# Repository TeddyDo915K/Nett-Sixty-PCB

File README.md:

# Nett Sixty PCB (An Inett Square X Replacement PCB)
This is a work in progress to create a replacement PCB for one of my favorite keyboards that I own.

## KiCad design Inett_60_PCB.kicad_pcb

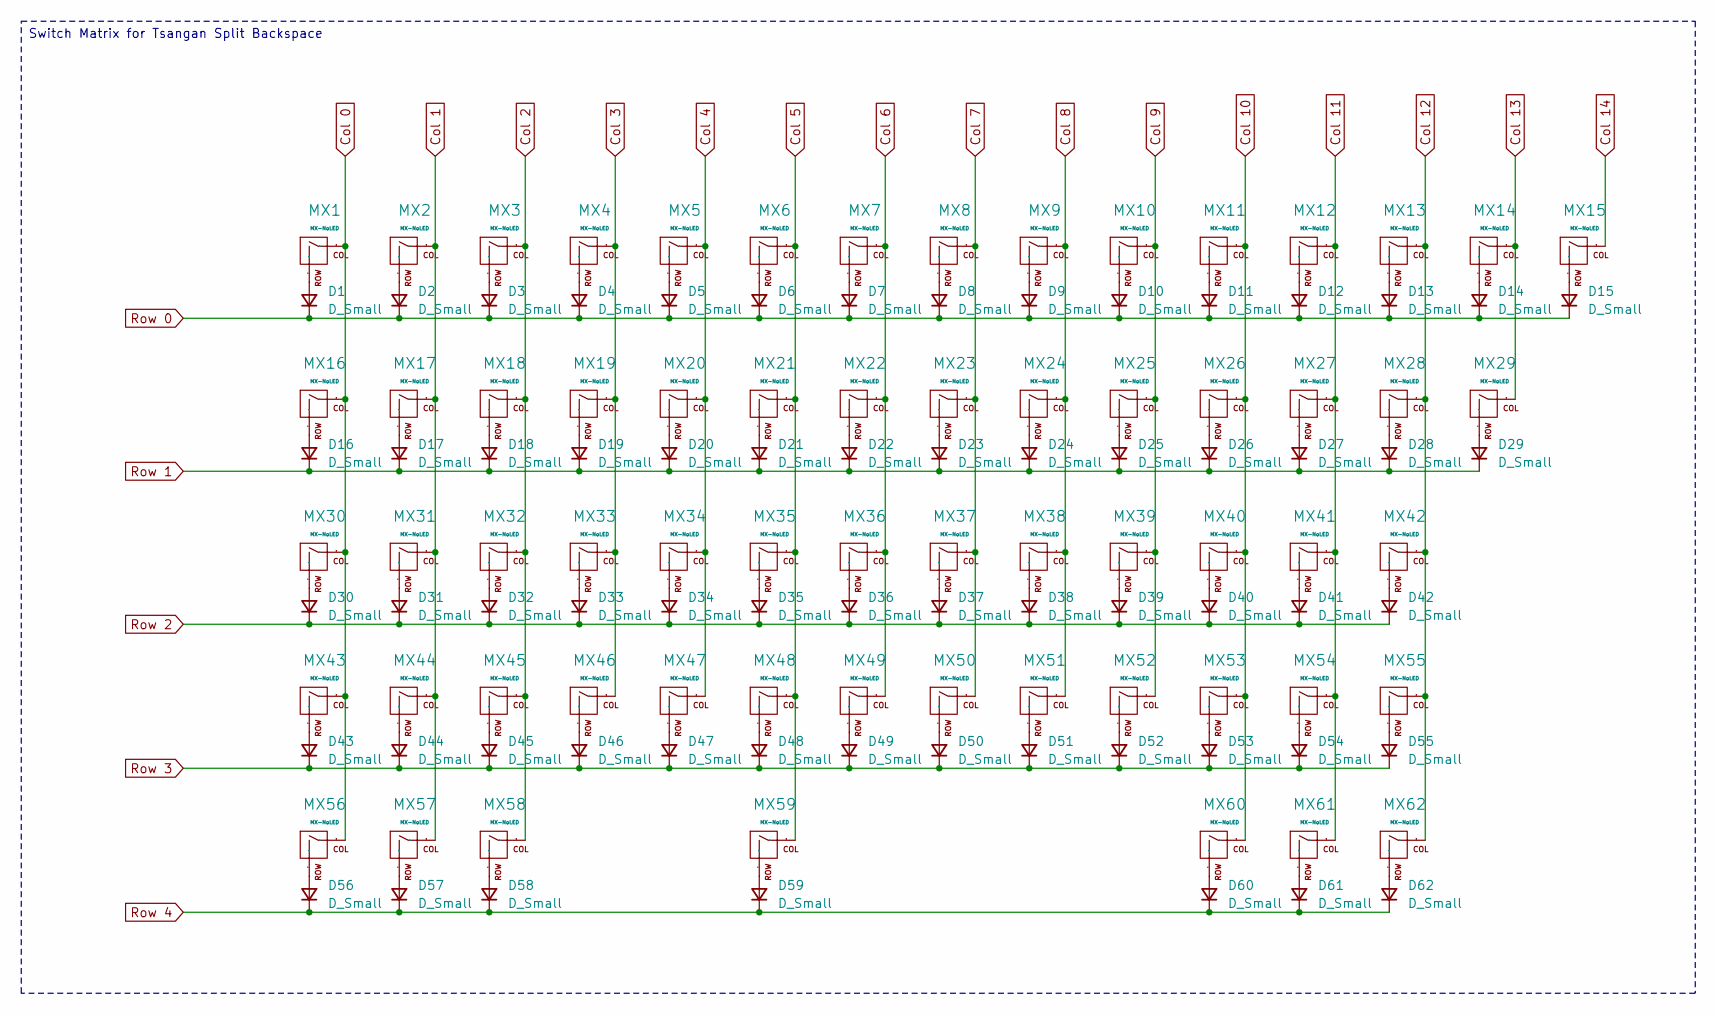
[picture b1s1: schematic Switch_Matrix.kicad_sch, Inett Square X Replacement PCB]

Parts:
D1, D2, D3, D4, D5, D6, D7, D8, D9, D10, D11, D12, D13, D14, D15, D16, D17, D18, D19, D20, D21, D22, D23, D24, D25, D26, D27, D28, D29, D30, D31, D32, D33, D34, D35, D36, D37, D38, D39, D40, D41, D42, D43, D44, D45, D46, D47, D48, D49, D50, D51, D52, D53, D54, D55, D56, D57, D58, D59, D60, D61, D62: D_Small; D_SOD-123
MX1, MX2, MX3, MX4, MX5, MX6, MX7, MX8, MX9, MX10, MX11, MX12, MX13, MX14, MX15, MX17, MX18, MX19, MX20, MX21, MX22, MX23, MX24, MX25, MX26, MX27, MX28, MX31, MX32, MX33, MX34, MX35, MX36, MX37, MX38, MX39, MX40, MX41, MX44, MX45, MX46, MX47, MX48, MX49, MX50, MX51, MX52, MX53, MX55, MX57, MX61: MX-NoLED; MXOnly-1U-Hotswap
MX16, MX29, MX56, MX58, MX60, MX62: MX-NoLED; MXOnly-1.5U-Hotswap
MX30, MX54: MX-NoLED; MXOnly-1.75U-Hotswap
MX42, MX43: MX-NoLED; MXOnly-2.25U-Hotswap
MX59: MX-NoLED; MXOnly-7U-Hotswap-ReversedStabilizers

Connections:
Col 0: MX1.1 (COL), MX16.1 (COL), MX30.1 (COL), MX43.1 (COL), MX56.1 (COL); also elsewhere on the board
Col 1: MX2.1 (COL), MX17.1 (COL), MX31.1 (COL), MX44.1 (COL), MX57.1 (COL); also elsewhere on the board
Col 2: MX3.1 (COL), MX18.1 (COL), MX32.1 (COL), MX45.1 (COL), MX58.1 (COL); also elsewhere on the board
Col 3: MX4.1 (COL), MX19.1 (COL), MX33.1 (COL), MX46.1 (COL); also elsewhere on the board
Col 4: MX5.1 (COL), MX20.1 (COL), MX34.1 (COL), MX47.1 (COL); also elsewhere on the board
Col 5: MX6.1 (COL), MX21.1 (COL), MX35.1 (COL), MX48.1 (COL), MX59.1 (COL); also elsewhere on the board
Col 6: MX7.1 (COL), MX22.1 (COL), MX36.1 (COL), MX49.1 (COL); also elsewhere on the board
Col 7: MX8.1 (COL), MX23.1 (COL), MX37.1 (COL), MX50.1 (COL); also elsewhere on the board
Col 8: MX9.1 (COL), MX24.1 (COL), MX38.1 (COL), MX51.1 (COL); also elsewhere on the board
Col 9: MX10.1 (COL), MX25.1 (COL), MX39.1 (COL), MX52.1 (COL); also elsewhere on the board
Col 10: MX11.1 (COL), MX26.1 (COL), MX40.1 (COL), MX53.1 (COL), MX60.1 (COL); also elsewhere on the board
Col 11: MX12.1 (COL), MX27.1 (COL), MX41.1 (COL), MX54.1 (COL), MX61.1 (COL); also elsewhere on the board
Col 12: MX13.1 (COL), MX28.1 (COL), MX42.1 (COL), MX55.1 (COL), MX62.1 (COL); also elsewhere on the board
Col 13: MX14.1 (COL), MX29.1 (COL); also elsewhere on the board
Col 14: MX15.1 (COL); also elsewhere on the board
unnamed: D1.2 (A), MX1.2 (ROW)
unnamed: D2.2 (A), MX2.2 (ROW)
unnamed: D3.2 (A), MX3.2 (ROW)
unnamed: D4.2 (A), MX4.2 (ROW)
unnamed: D5.2 (A), MX5.2 (ROW)
unnamed: D6.2 (A), MX6.2 (ROW)
unnamed: D7.2 (A), MX7.2 (ROW)
unnamed: D8.2 (A), MX8.2 (ROW)
unnamed: D9.2 (A), MX9.2 (ROW)
unnamed: D10.2 (A), MX10.2 (ROW)
unnamed: D11.2 (A), MX11.2 (ROW)
unnamed: D12.2 (A), MX12.2 (ROW)
unnamed: D13.2 (A), MX13.2 (ROW)
unnamed: D14.2 (A), MX14.2 (ROW)
unnamed: D15.2 (A), MX15.2 (ROW)
unnamed: D16.2 (A), MX16.2 (ROW)
unnamed: D17.2 (A), MX17.2 (ROW)
unnamed: D18.2 (A), MX18.2 (ROW)
unnamed: D19.2 (A), MX19.2 (ROW)
unnamed: D20.2 (A), MX20.2 (ROW)
unnamed: D21.2 (A), MX21.2 (ROW)
unnamed: D22.2 (A), MX22.2 (ROW)
unnamed: D23.2 (A), MX23.2 (ROW)
unnamed: D24.2 (A), MX24.2 (ROW)
unnamed: D25.2 (A), MX25.2 (ROW)
unnamed: D26.2 (A), MX26.2 (ROW)
unnamed: D27.2 (A), MX27.2 (ROW)
unnamed: D28.2 (A), MX28.2 (ROW)
unnamed: D29.2 (A), MX29.2 (ROW)
unnamed: D30.2 (A), MX30.2 (ROW)
unnamed: D31.2 (A), MX31.2 (ROW)
unnamed: D32.2 (A), MX32.2 (ROW)
unnamed: D33.2 (A), MX33.2 (ROW)
unnamed: D34.2 (A), MX34.2 (ROW)
unnamed: D35.2 (A), MX35.2 (ROW)
unnamed: D36.2 (A), MX36.2 (ROW)
unnamed: D37.2 (A), MX37.2 (ROW)
unnamed: D38.2 (A), MX38.2 (ROW)
unnamed: D39.2 (A), MX39.2 (ROW)
unnamed: D40.2 (A), MX40.2 (ROW)
unnamed: D41.2 (A), MX41.2 (ROW)
unnamed: D42.2 (A), MX42.2 (ROW)
unnamed: D43.2 (A), MX43.2 (ROW)
unnamed: D44.2 (A), MX44.2 (ROW)
unnamed: D45.2 (A), MX45.2 (ROW)
unnamed: D46.2 (A), MX46.2 (ROW)
unnamed: D47.2 (A), MX47.2 (ROW)
unnamed: D48.2 (A), MX48.2 (ROW)
unnamed: D49.2 (A), MX49.2 (ROW)
unnamed: D50.2 (A), MX50.2 (ROW)
unnamed: D51.2 (A), MX51.2 (ROW)
unnamed: D52.2 (A), MX52.2 (ROW)
unnamed: D53.2 (A), MX53.2 (ROW)
unnamed: D54.2 (A), MX54.2 (ROW)
unnamed: D55.2 (A), MX55.2 (ROW)
unnamed: D56.2 (A), MX56.2 (ROW)
unnamed: D57.2 (A), MX57.2 (ROW)
unnamed: D58.2 (A), MX58.2 (ROW)
unnamed: D59.2 (A), MX59.2 (ROW)
unnamed: D60.2 (A), MX60.2 (ROW)
unnamed: D61.2 (A), MX61.2 (ROW)
unnamed: D62.2 (A), MX62.2 (ROW)
Row 0: D1.1 (K), D2.1 (K), D3.1 (K), D4.1 (K), D5.1 (K), D6.1 (K), D7.1 (K), D8.1 (K), D9.1 (K), D10.1 (K), D11.1 (K), D12.1 (K), D13.1 (K), D14.1 (K), D15.1 (K); also elsewhere on the board
Row 1: D16.1 (K), D17.1 (K), D18.1 (K), D19.1 (K), D20.1 (K), D21.1 (K), D22.1 (K), D23.1 (K), D24.1 (K), D25.1 (K), D26.1 (K), D27.1 (K), D28.1 (K), D29.1 (K); also elsewhere on the board
Row 2: D30.1 (K), D31.1 (K), D32.1 (K), D33.1 (K), D34.1 (K), D35.1 (K), D36.1 (K), D37.1 (K), D38.1 (K), D39.1 (K), D40.1 (K), D41.1 (K), D42.1 (K); also elsewhere on the board
Row 3: D43.1 (K), D44.1 (K), D45.1 (K), D46.1 (K), D47.1 (K), D48.1 (K), D49.1 (K), D50.1 (K), D51.1 (K), D52.1 (K), D53.1 (K), D54.1 (K), D55.1 (K); also elsewhere on the board
Row 4: D56.1 (K), D57.1 (K), D58.1 (K), D59.1 (K), D60.1 (K), D61.1 (K), D62.1 (K); also elsewhere on the board

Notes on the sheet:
Switch Matrix for Tsangan Split Backspace

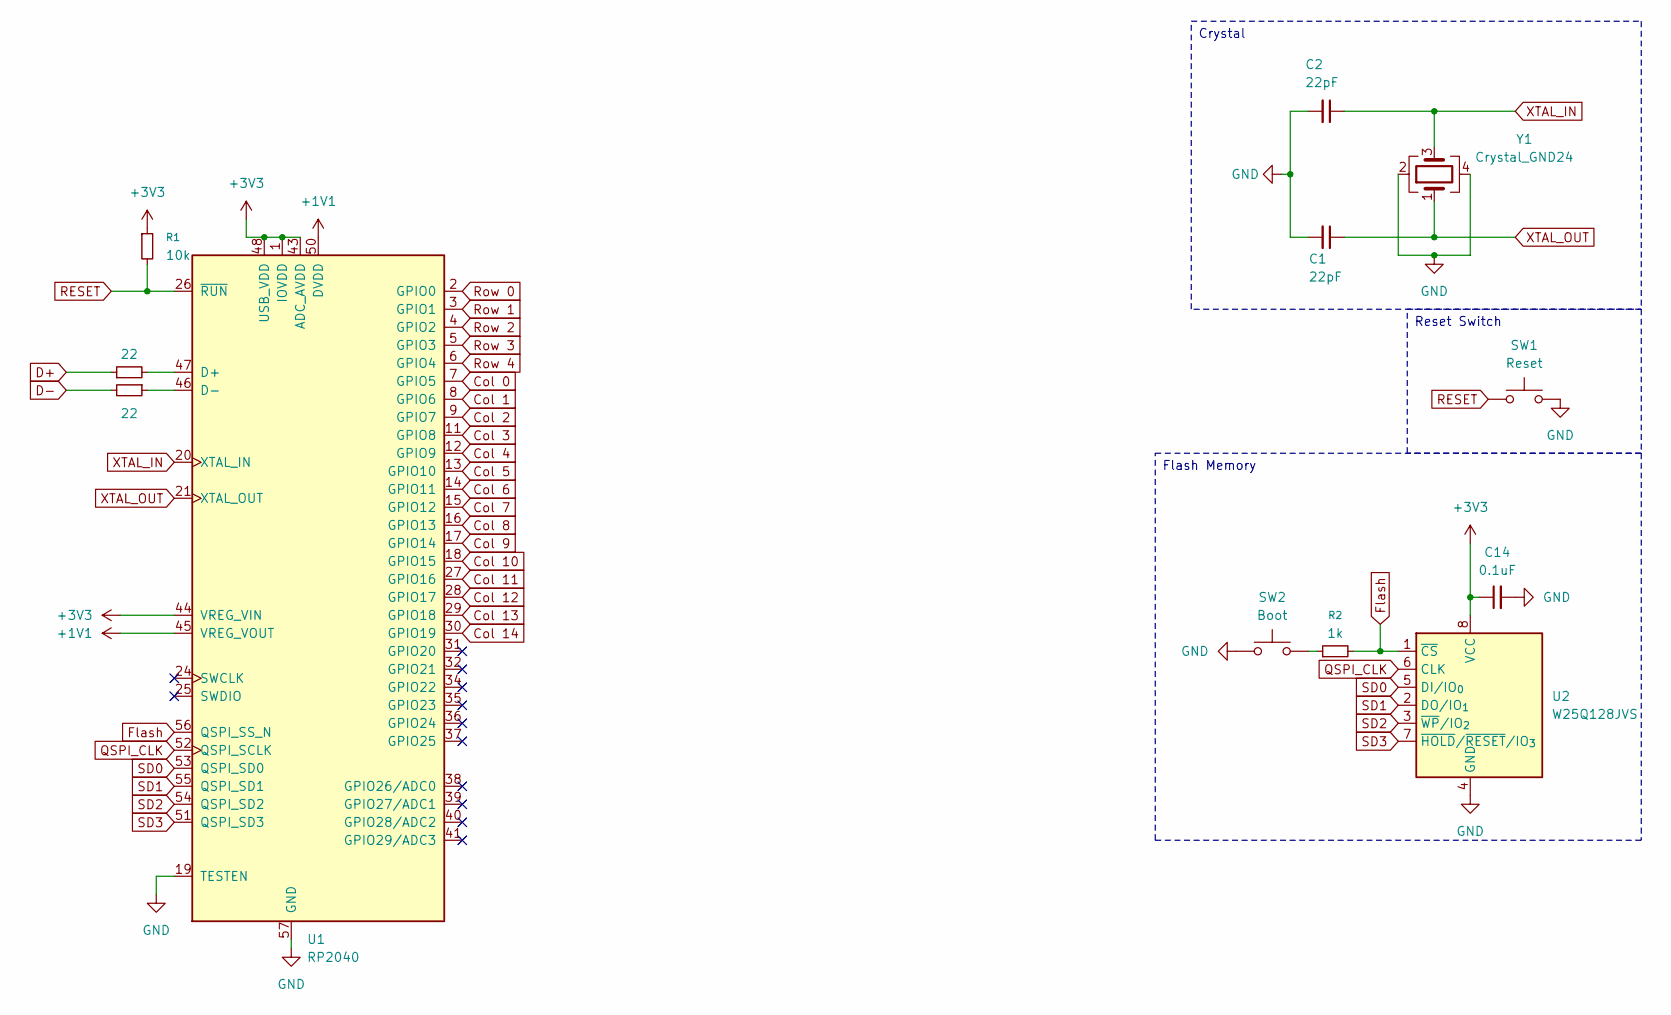
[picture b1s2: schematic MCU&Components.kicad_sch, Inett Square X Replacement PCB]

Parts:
C1, C2: 22pF; C_0402_1005Metric
C14: 0.1uF; C_0402
R1: 10k; R_0805_2012Metric_Pad1.20x1.40mm_HandSolder
R2: 1k; R_0805_2012Metric_Pad1.20x1.40mm_HandSolder
R5, R6: 22; R_0402
SW1: Reset; TS-1088R-02026; MPN TS-1088R-02026; LCSC C455280
SW2: Boot; TS-1088R-02026; MPN TS-1088R-02026; LCSC C455280
U1: RP2040; RP2040-QFN-56
U2: W25Q128JVS; SOIC-8_5.3x5.3mm_P1.27mm
Y1: Crystal_GND24; Crystal_SMD_3225-4Pin_3.2x2.5mm

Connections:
+1V1: U1.23 (DVDD), U1.45 (VREG_VOUT), U1.50 (DVDD); also elsewhere on the board
+3V3: C14.1, R1.1, U1.1 (IOVDD), U1.10 (IOVDD), U1.22 (IOVDD), U1.33 (IOVDD), U1.42 (IOVDD), U1.43 (ADC_AVDD), U1.44 (VREG_VIN), U1.48 (USB_VDD), U1.49 (IOVDD), U2.8 (VCC); also elsewhere on the board
Col 0: U1.7 (GPIO5); also elsewhere on the board
Col 1: U1.8 (GPIO6); also elsewhere on the board
Col 2: U1.9 (GPIO7); also elsewhere on the board
Col 3: U1.11 (GPIO8); also elsewhere on the board
Col 4: U1.12 (GPIO9); also elsewhere on the board
Col 5: U1.13 (GPIO10); also elsewhere on the board
Col 6: U1.14 (GPIO11); also elsewhere on the board
Col 7: U1.15 (GPIO12); also elsewhere on the board
Col 8: U1.16 (GPIO13); also elsewhere on the board
Col 9: U1.17 (GPIO14); also elsewhere on the board
Col 10: U1.18 (GPIO15); also elsewhere on the board
Col 11: U1.27 (GPIO16); also elsewhere on the board
Col 12: U1.28 (GPIO17); also elsewhere on the board
Col 13: U1.29 (GPIO18); also elsewhere on the board
Col 14: U1.30 (GPIO19); also elsewhere on the board
D+: R5.1; also elsewhere on the board
D-: R6.2; also elsewhere on the board
Flash: R2.2, U1.56 (QSPI_SS_N), U2.1 (~CS)
GND: C1.2, C2.2, C14.2, SW1.2, SW2.1, U1.19 (TESTEN), U1.57 (GND), U2.4 (GND), Y1.2, Y1.4; also elsewhere on the board
unnamed: R2.1, SW2.2
unnamed: R5.2, U1.47 (D+)
unnamed: R6.1, U1.46 (D-)
QSPI_CLK: U1.52 (QSPI_SCLK), U2.6 (CLK)
RESET: R1.2, SW1.1, U1.26 (~RUN)
Row 0: U1.2 (GPIO0); also elsewhere on the board
Row 1: U1.3 (GPIO1); also elsewhere on the board
Row 2: U1.4 (GPIO2); also elsewhere on the board
Row 3: U1.5 (GPIO3); also elsewhere on the board
Row 4: U1.6 (GPIO4); also elsewhere on the board
SD0: U1.53 (QSPI_SD0), U2.5 (DI/IO_{0})
SD1: U1.55 (QSPI_SD1), U2.2 (DO/IO_{1})
SD2: U1.54 (QSPI_SD2), U2.3 (~WP/IO_{2})
SD3: U1.51 (QSPI_SD3), U2.7 (~HOLD/~RESET/IO_{3})
XTAL_IN: C2.1, U1.20 (XTAL_IN), Y1.3
XTAL_OUT: C1.1, U1.21 (XTAL_OUT), Y1.1

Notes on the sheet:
Crystal
Flash Memory
Reset Switch

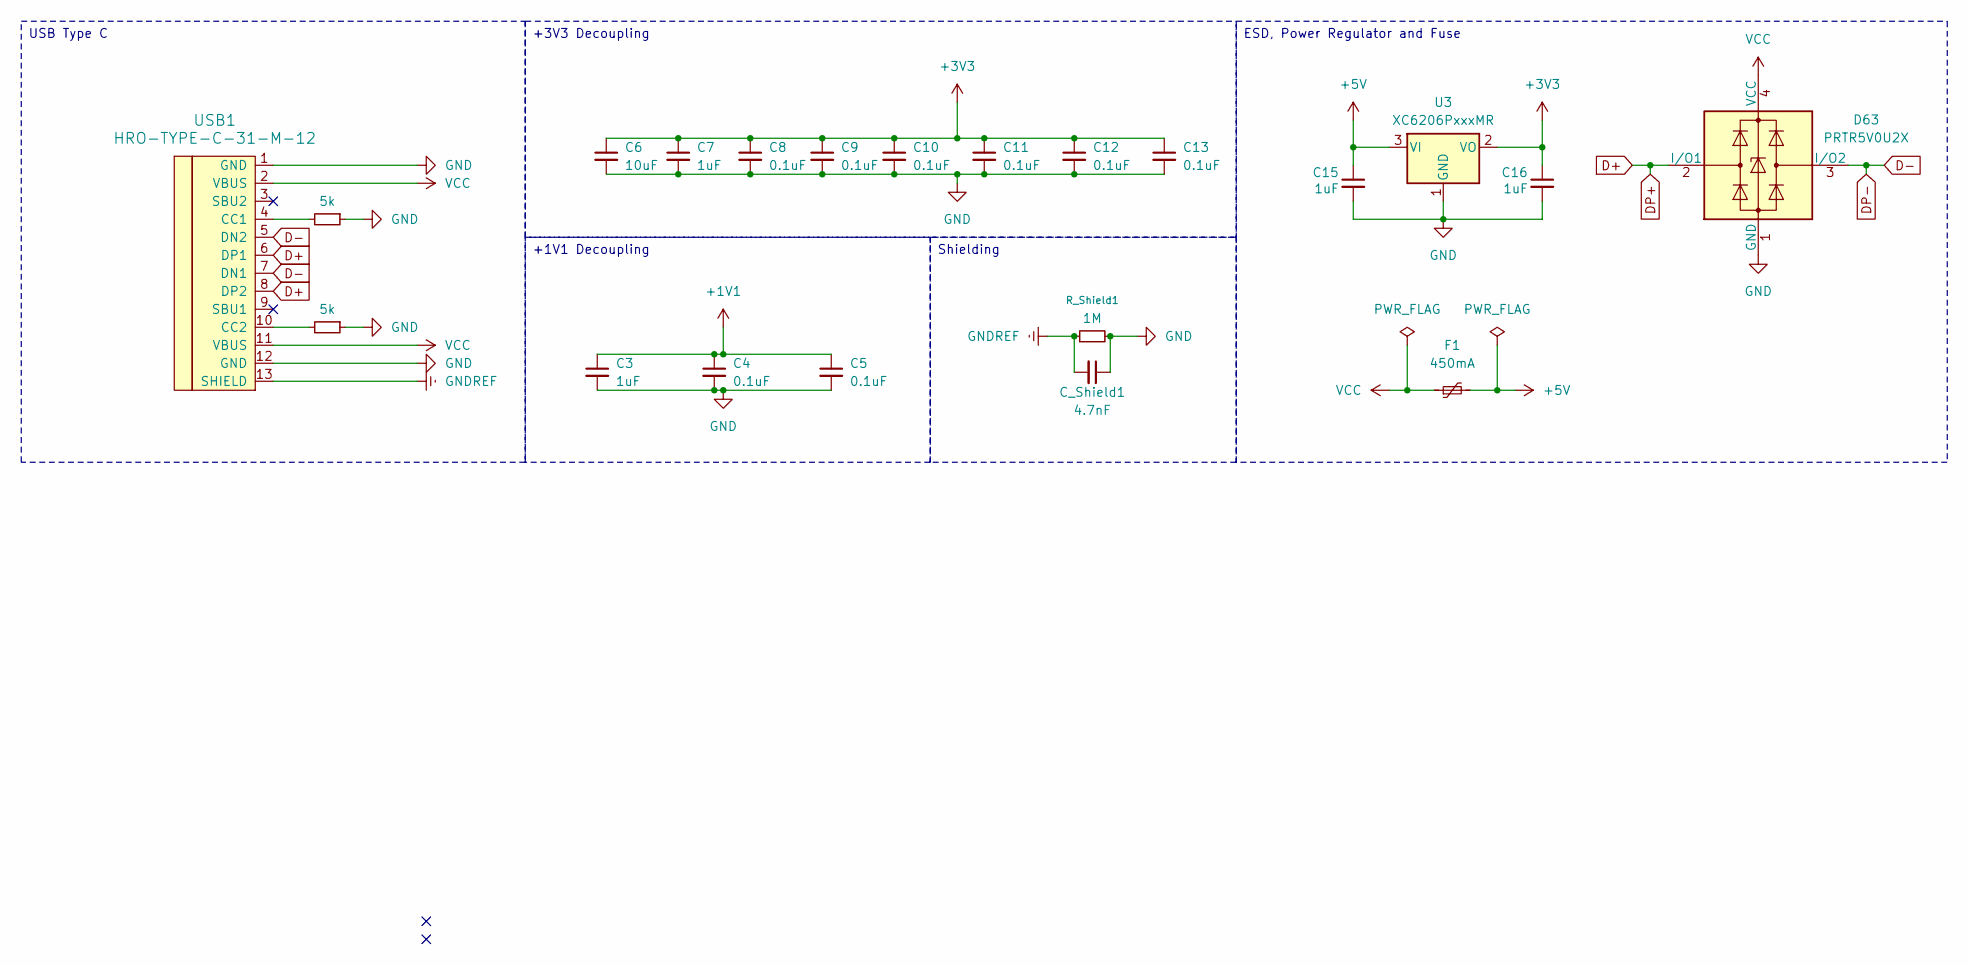
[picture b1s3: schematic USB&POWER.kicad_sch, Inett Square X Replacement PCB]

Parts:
C3, C7, C15, C16: 1uF; C_0402
C4, C5, C8, C9, C10, C11, C12, C13: 0.1uF; C_0402
C6: 10uF; C_0402
C_Shield1: 4.7nF; C_0402
D63: PRTR5V0U2X; SOT-143
F1: 450mA; Fuse_0805_2012Metric
R3, R4: 5k; R_0402
R_Shield1: 1M; R_0402
U3: XC6206PxxxMR; SOT-23-3
USB1: HRO-TYPE-C-31-M-12

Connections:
+1V1: C3.1, C4.1, C5.1; also elsewhere on the board
+3V3: C6.1, C7.1, C8.1, C9.1, C10.1, C11.1, C12.1, C13.1, C16.1, U3.2 (VO); also elsewhere on the board
+5V: C15.1, F1.2, U3.3 (VI)
D+: D63.2 (I/O1), USB1.6 (DP1), USB1.8 (DP2); also elsewhere on the board
D-: D63.3 (I/O2), USB1.5 (DN2), USB1.7 (DN1); also elsewhere on the board
GND: C3.2, C4.2, C5.2, C6.2, C7.2, C8.2, C9.2, C10.2, C11.2, C12.2, C13.2, C15.2, C16.2, C_Shield1.1, D63.1 (GND), R3.1, R4.1, R_Shield1.2, U3.1 (GND), USB1.1 (GND), USB1.12 (GND); also elsewhere on the board
GNDREF: C_Shield1.2, R_Shield1.1, USB1.13 (SHIELD); also elsewhere on the board
unnamed: R4.2, USB1.4 (CC1)
unnamed: R3.2, USB1.10 (CC2)
VCC: D63.4 (VCC), F1.1, USB1.2 (VBUS), USB1.11 (VBUS)

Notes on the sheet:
+1V1 Decoupling
Shielding
+3V3 Decoupling
ESD, Power Regulator and Fuse
USB Type C

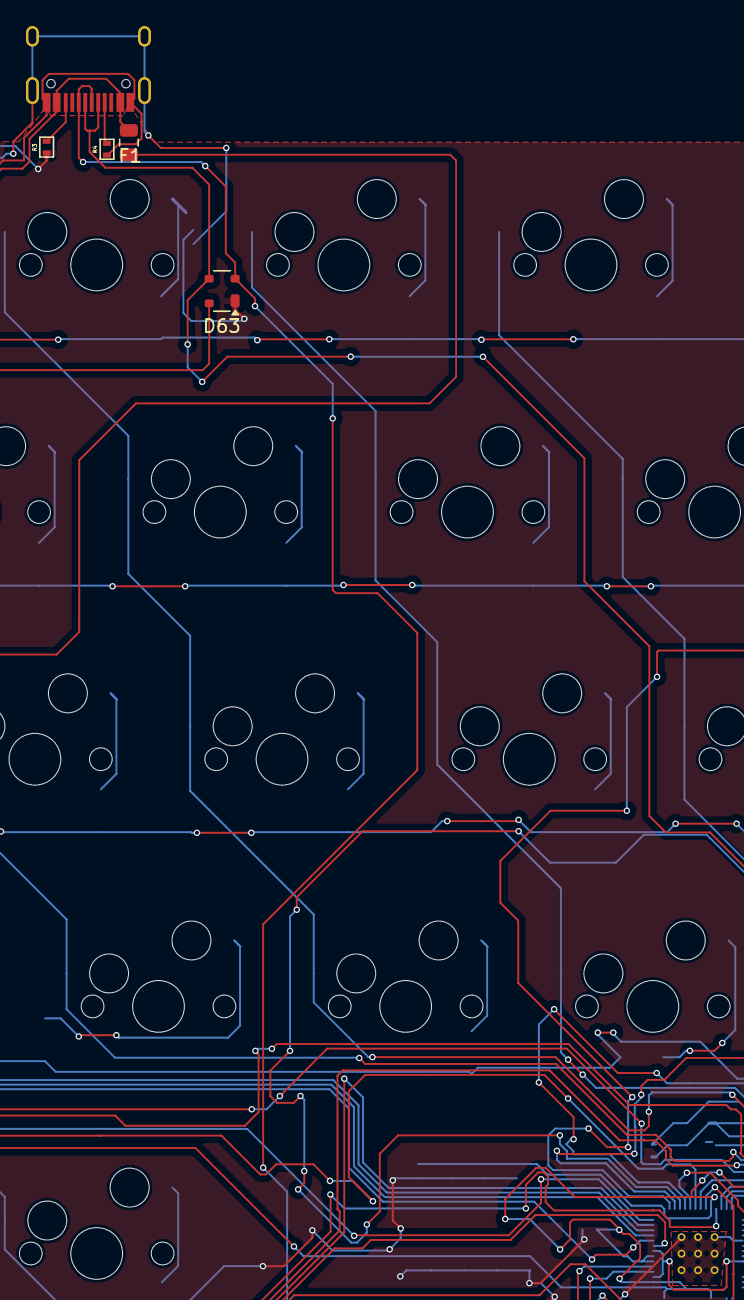
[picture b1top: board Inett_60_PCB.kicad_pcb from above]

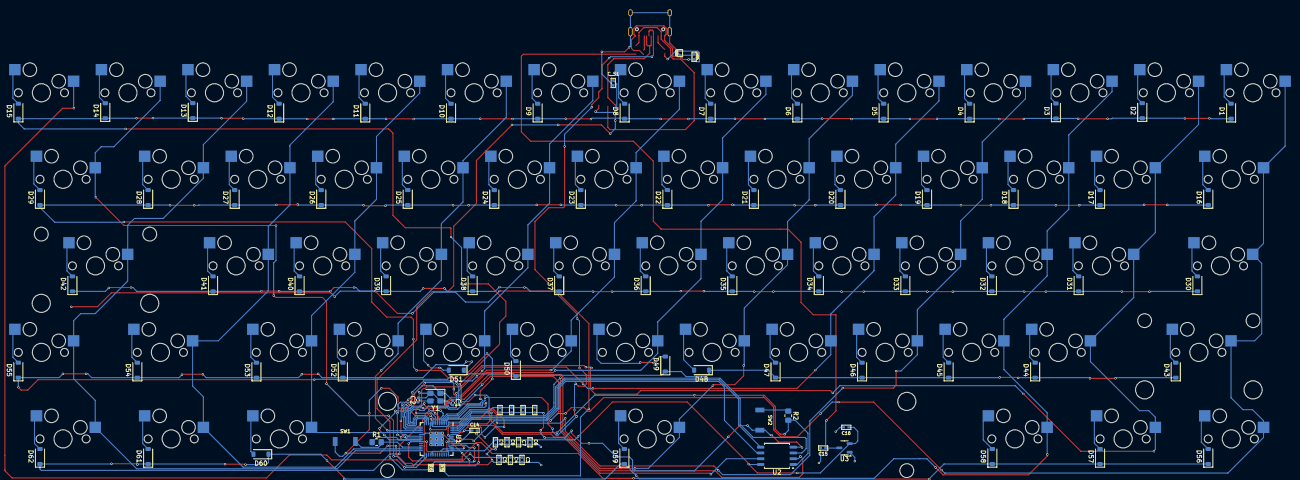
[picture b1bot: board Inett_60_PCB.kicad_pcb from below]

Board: 2 copper layers, 158 parts (91 on the bottom side), 104 nets.

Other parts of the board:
C_S1: 4.7nF; C_0402

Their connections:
GND: C_S1.1; also elsewhere on the board
GNDREF: C_S1.2; also elsewhere on the board
